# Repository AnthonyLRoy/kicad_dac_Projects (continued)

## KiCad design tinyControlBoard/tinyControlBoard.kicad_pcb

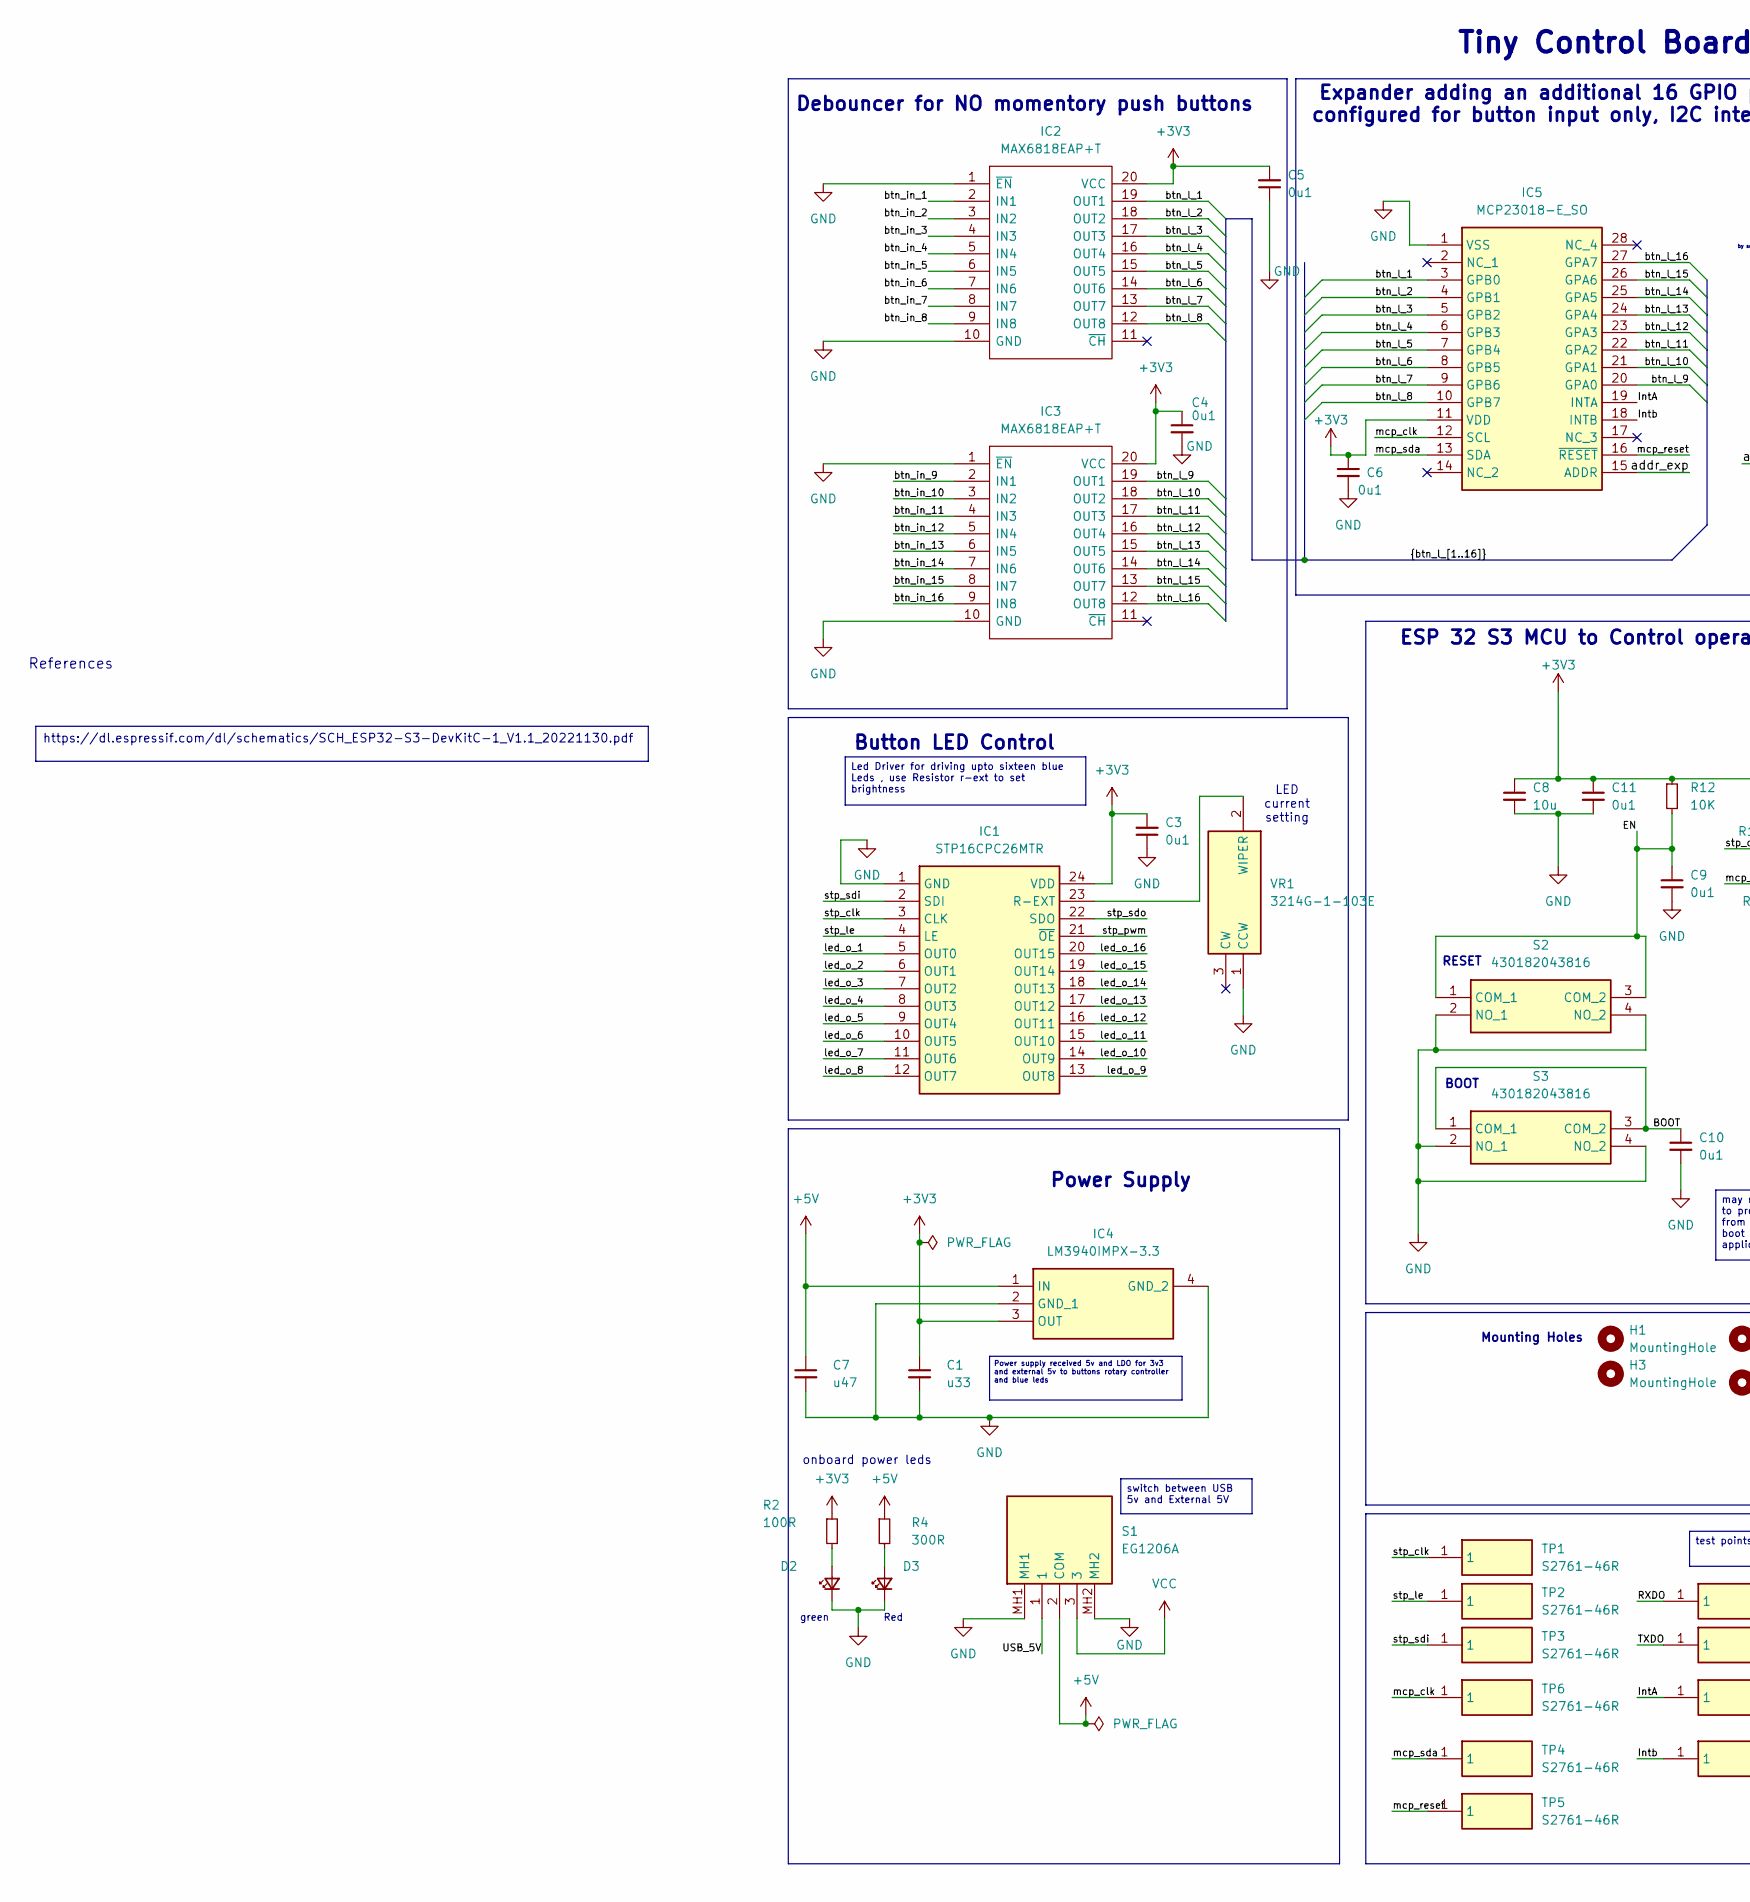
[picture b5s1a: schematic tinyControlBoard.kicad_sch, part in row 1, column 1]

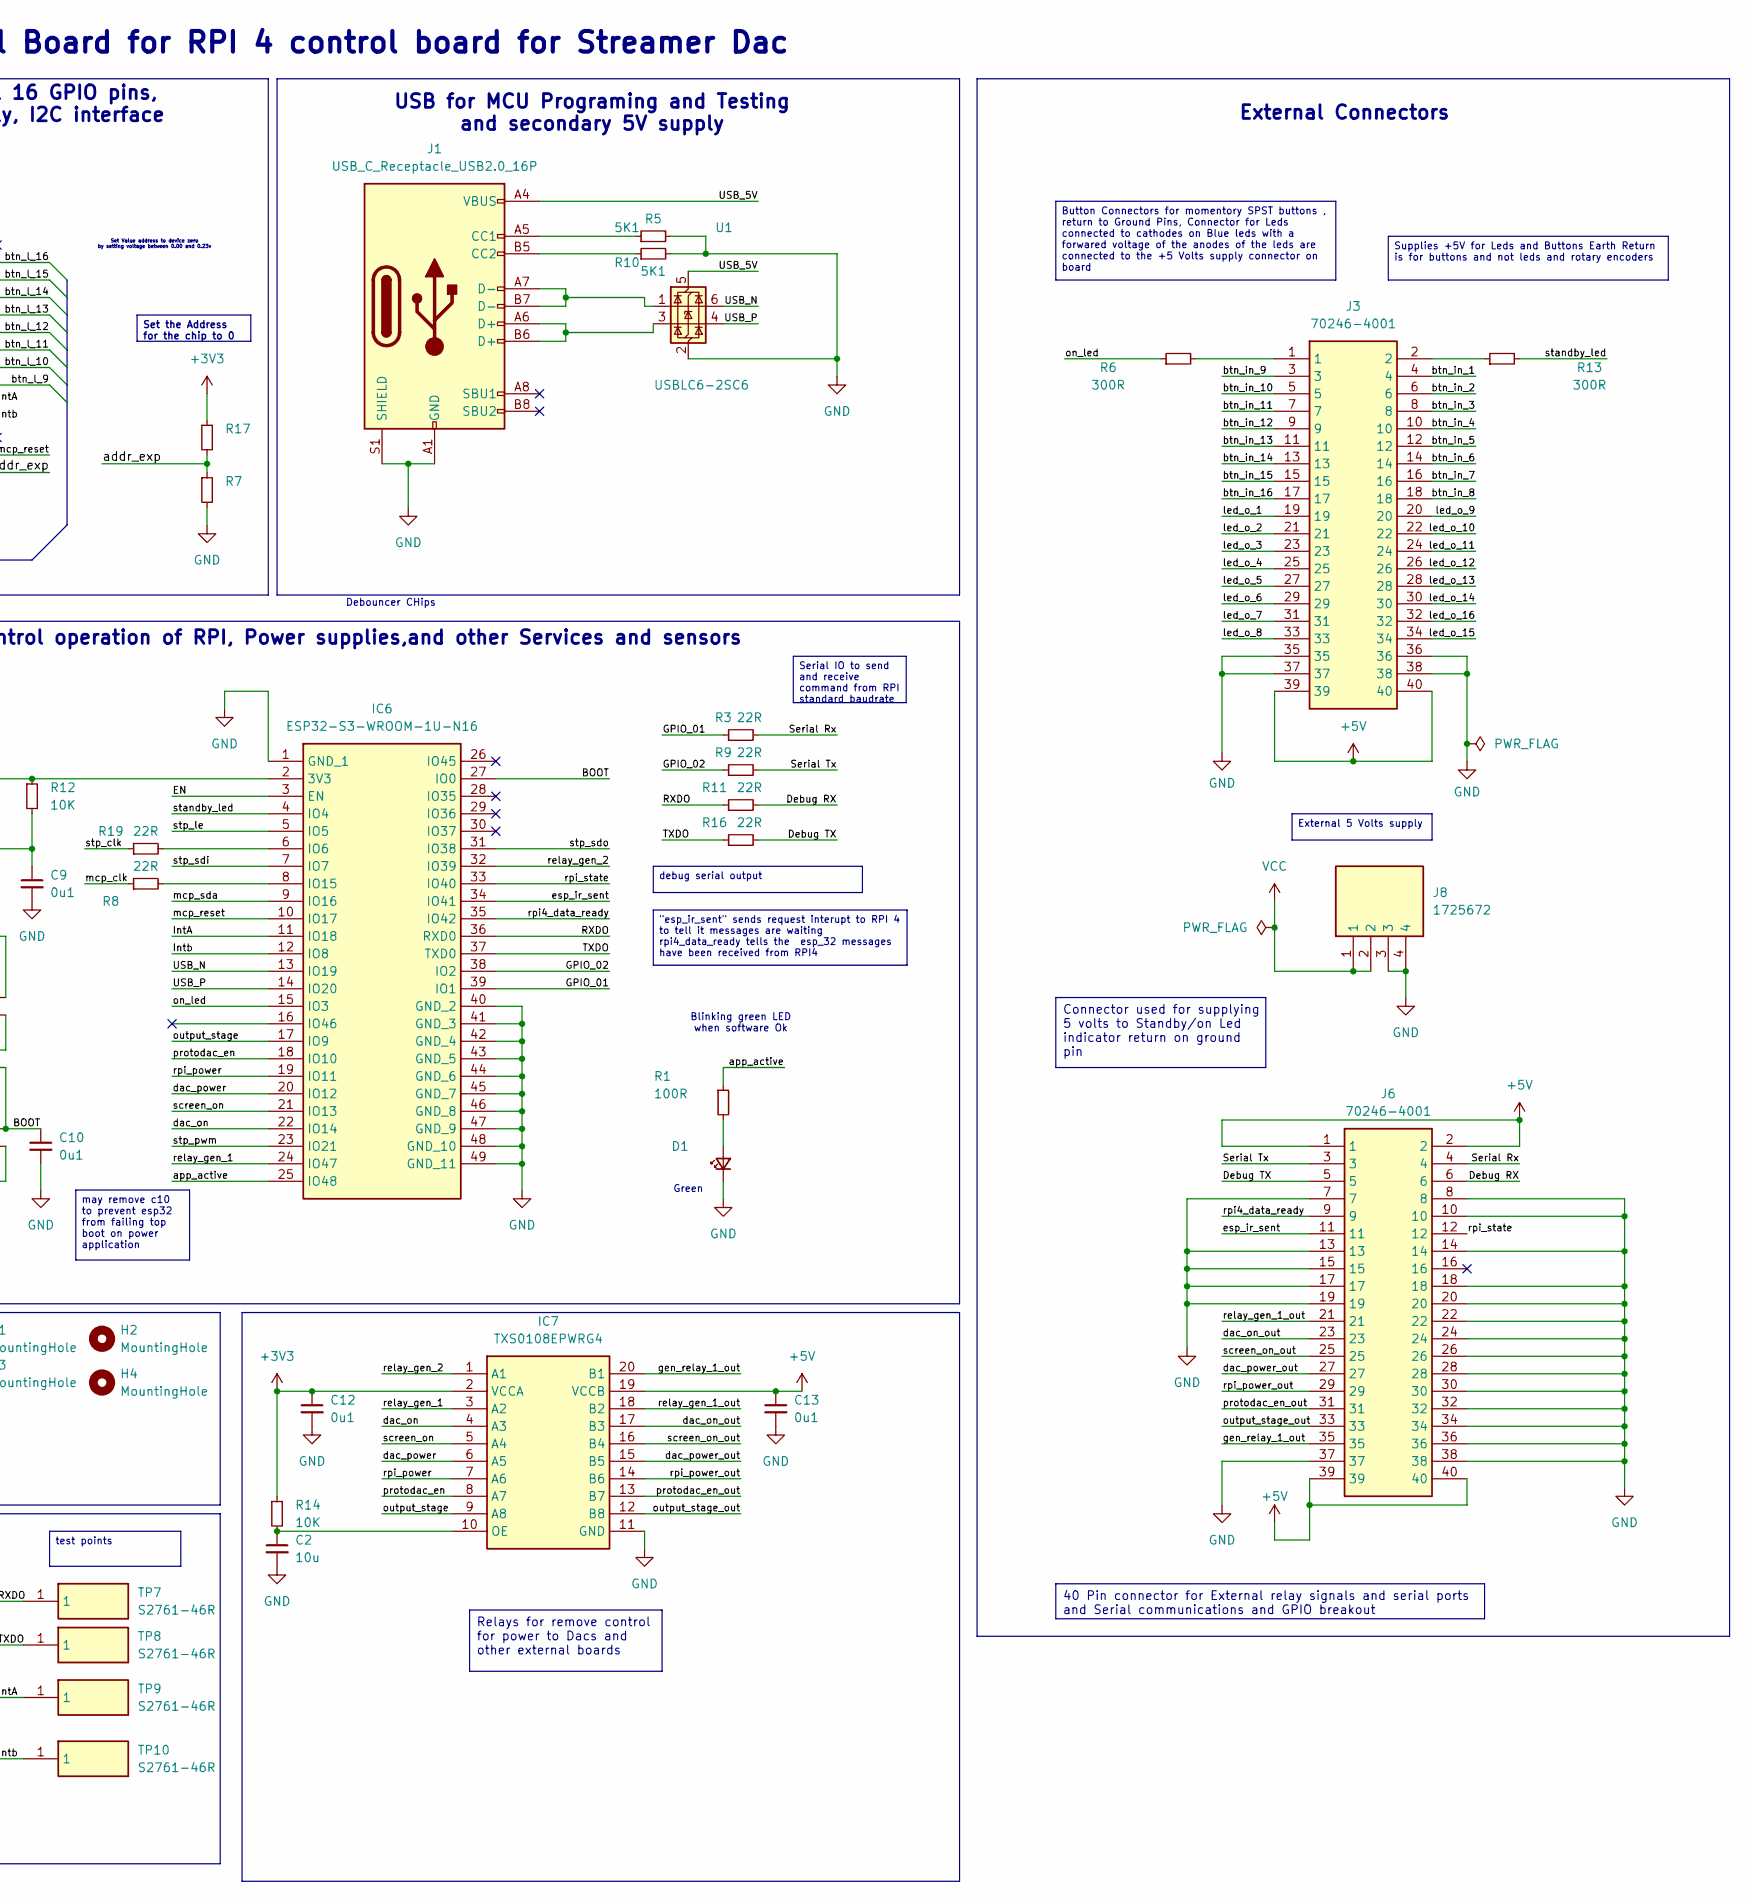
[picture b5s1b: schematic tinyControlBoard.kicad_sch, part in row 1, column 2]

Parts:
C1: u33; CAPC1608X90N; Mouser Part Number 581-0603YC334JAT2A
C2, C8: 10u; CAPC1608X90N; Mouser Part Number 581-0603YD106MAT2A
C3, C4, C5, C6, C9, C10: 0u1; CAPC1608X87N; Manufacturer_Part_Number C0603C104K4RAC3190
C7: u47; CAPC1608X90N; Mouser Part Number 81-GCM188R71C474KA5J
C11, C12, C13: 0u1; CAPC1608X87N; Mouser Part Number 80-C0603C104K4R3190
D1, D2: LG_R971-KN-1; LEDC2012X80N; Mouser Part Number 720-LGR971-KN-1
D3: LS_R976; LEDC2012X40N; Mouser Part Number 720-LSR976D5178
H1, H2, H3, H4: MountingHole; MountingHole_2.5mm
IC1: STP16CPC26MTR; SOIC127P1032X265-24N; Mouser Part Number 511-STP16CPC26MTR
IC2, IC3: MAX6818EAP+T; SSOP-20_5.3x7.2mm_P0.65mm; Manufacturer_Part_Number MAX6818EAP+T; Mouser Part Number 700-MAX6818EAPT
IC4: LM3940IMPX-3.3; SOT230P700X180-4N; Mouser Part Number 926-LM3940IMPX-33
IC5: MCP23018-E_SO; SOIC127P1030X265-28N; Mouser Part Number 579-MCP23018-E/SO
IC6: ESP32-S3-WROOM-1U-N16; ESP32S3WROOM1UN16; Mouser Part Number 356-ESP32S3WROM1UN16
IC7: TXS0108EPWRG4; SOP65P640X120-20N; Mouser Part Number 595-TXS0108EPWRG4
J1: USB_C_Receptacle_USB2.0_16P; USB_C_Receptacle_GCT_USB4105-xx-A_16P_TopMnt_Horizontal; Manufacturer_Part_Number USB4105-GF-A-120; Mouser Part Number 640-USB4105-GF-A-120
J3, J6: 70246-4001; SHDR40W64P254_2X20_5842X889X947P; Mouser Part Number 538-70246-4001
J8: 1725672; Mouser Part Number 651-1725672
R1, R2: 100R; ERJH3; Mouser Part Number 667-ERJ-H3EF1200V
R3, R8, R9, R11, R16, R19: 22R; RESC1609X55N; Mouser Part Number 667-ERJ-P03F22R0V
R4, R6, R13: 300R; ERJH3; Mouser Part Number 667-ERJ-H3ED3000V
R5, R10: 5K1; RESC1608X55N; Mouser Part Number 755-ESR03EZPJ512
R7: MCT0603PD1001DP500; RESC1608X55N; Mouser Part Number 594-MCT0603PD1001DP5
R12, R14: 10K; RESC1608X50N; Mouser Part Number 71-CRCW060310K0FKEI
R17: TNPW060315K0BEEA; RESC1608X60N; Mouser Part Number 71-TNPW060315K0BEEA
S1: EG1206A; Mouser Part Number 612-EG1206A
S2, S3: 430182043816; Mouser Part Number 710-430182043816
TP1, TP2, TP3, TP4, TP5, TP6, TP7, TP8, TP9, TP10: S2761-46R; S276146R; Mouser Part Number 855-S2761-46R
U1: USBLC6-2SC6; SOT-23-6; Manufacturer_Part_Number 511-USBLC6-2SC6; Mouser Part Number USBLC6-2SC6
VR1: 3214G-1-103E; 3214G1103E; Mouser Part Number 652-3214G-1-103E

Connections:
+3V3: C1.1, C3.2, C4.1, C5.2, C6.1, C8.1, C11.1, C12.1, IC1.24 (VDD), IC2.20 (VCC), IC3.20 (VCC), IC4.3 (OUT), IC5.11 (VDD), IC6.2 (3V3), IC7.2 (VCCA), R2.1, R12.1, R14.1, R17.1
+5V: C7.1, C13.1, IC4.1 (IN), IC7.19 (VCCB), J3.39, J3.40, J6.1, J6.2, J6.39, J6.40, R4.1, S1.2 (COM)
/BOOT: C10.1, IC6.27 (IO0), S3.1 (COM_1), S3.3 (COM_2)
/Debug RX: J6.6, R11.2
/Debug TX: J6.5, R16.2
/EN: C9.1, IC6.3 (EN), R12.2, S2.1 (COM_1), S2.3 (COM_2)
/GPIO_01: IC6.39 (IO1), R3.1
/GPIO_02: IC6.38 (IO2), R9.1
/GPIO_39: IC6.32 (IO39), IC7.1 (A1)
/IntA: IC5.19 (INTA), IC6.11 (IO18), TP9.1
/Intb: IC5.18 (INTB), IC6.12 (IO8), TP10.1
/RXDO: IC6.36 (RXD0), R11.1, TP7.1
/Serial Rx: J6.4, R3.2
/Serial Tx: J6.3, R9.2
/TXDO: IC6.37 (TXD0), R16.1, TP8.1
/USB_5V: J1.A4 (VBUS), J1.A9 (VBUS), J1.B4 (VBUS), J1.B9 (VBUS), S1.1, U1.5 (VBUS)
/USB_N: IC6.13 (IO19), U1.6 (I/O1)
/USB_P: IC6.14 (IO20), U1.4 (I/O2)
/addr_exp: IC5.15 (ADDR), R7.1, R17.2
/app_active: IC6.25 (IO48), R1.1
/btn_in_1: IC2.2 (IN1), J3.4
/btn_in_2: IC2.3 (IN2), J3.6
/btn_in_3: IC2.4 (IN3), J3.8
/btn_in_4: IC2.5 (IN4), J3.10
/btn_in_5: IC2.6 (IN5), J3.12
/btn_in_6: IC2.7 (IN6), J3.14
/btn_in_7: IC2.8 (IN7), J3.16
/btn_in_8: IC2.9 (IN8), J3.18
/btn_in_9: IC3.2 (IN1), J3.3
/btn_in_10: IC3.3 (IN2), J3.5
/btn_in_11: IC3.4 (IN3), J3.7
/btn_in_12: IC3.5 (IN4), J3.9
/btn_in_13: IC3.6 (IN5), J3.11
/btn_in_14: IC3.7 (IN6), J3.13
/btn_in_15: IC3.8 (IN7), J3.15
/btn_in_16: IC3.9 (IN8), J3.17
/btn_l_1: IC2.19 (OUT1), IC5.3 (GPB0)
/btn_l_2: IC2.18 (OUT2), IC5.4 (GPB1)
/btn_l_3: IC2.17 (OUT3), IC5.5 (GPB2)
/btn_l_4: IC2.16 (OUT4), IC5.6 (GPB3)
/btn_l_5: IC2.15 (OUT5), IC5.7 (GPB4)
/btn_l_6: IC2.14 (OUT6), IC5.8 (GPB5)
/btn_l_7: IC2.13 (OUT7), IC5.9 (GPB6)
/btn_l_8: IC2.12 (OUT8), IC5.10 (GPB7)
/btn_l_9: IC3.19 (OUT1), IC5.20 (GPA0)
/btn_l_10: IC3.18 (OUT2), IC5.21 (GPA1)
/btn_l_11: IC3.17 (OUT3), IC5.22 (GPA2)
/btn_l_12: IC3.16 (OUT4), IC5.23 (GPA3)
/btn_l_13: IC3.15 (OUT5), IC5.24 (GPA4)
/btn_l_14: IC3.14 (OUT6), IC5.25 (GPA5)
/btn_l_15: IC3.13 (OUT7), IC5.26 (GPA6)
/btn_l_16: IC3.12 (OUT8), IC5.27 (GPA7)
/dac_on: IC6.22 (IO14), IC7.4 (A3)
/dac_on_out: IC7.17 (B3), J6.23
/esp_ir_sent: IC6.34 (IO41), J6.11
/gen_relay_1_out: IC7.20 (B1), J6.35
/gen_relay_2: IC6.18 (IO10), IC7.8 (A7)
/gen_relay_2_out: IC7.13 (B7), J6.31
/gen_relay_3: IC6.17 (IO9), IC7.9 (A8)
/gen_relay_3_out: IC7.12 (B8), J6.33
/gen_relay_4: IC6.24 (IO47), IC7.3 (A2)
/gen_relay_4_out: IC7.18 (B2), J6.21
/led_o_1: IC1.5 (OUT0), J3.19
/led_o_2: IC1.6 (OUT1), J3.21
/led_o_3: IC1.7 (OUT2), J3.23
/led_o_4: IC1.8 (OUT3), J3.25
/led_o_5: IC1.9 (OUT4), J3.27
/led_o_6: IC1.10 (OUT5), J3.29
/led_o_7: IC1.11 (OUT6), J3.31
/led_o_8: IC1.12 (OUT7), J3.33
/led_o_9: IC1.13 (OUT8), J3.20
/led_o_10: IC1.14 (OUT9), J3.22
/led_o_11: IC1.15 (OUT10), J3.24
/led_o_12: IC1.16 (OUT11), J3.26
/led_o_13: IC1.17 (OUT12), J3.28
/led_o_14: IC1.18 (OUT13), J3.30
/led_o_15: IC1.19 (OUT14), J3.34
/led_o_16: IC1.20 (OUT15), J3.32
/mains_power: IC6.19 (IO11), IC7.7 (A6)
/mains_power_out: IC7.14 (B6), J6.29
/mcp_clk: IC5.12 (SCL), R8.1, TP6.1
/mcp_reset: IC5.16 (~RESET), IC6.10 (IO17), TP5.1
/mcp_sda: IC5.13 (SDA), IC6.9 (IO16), TP4.1
/on_led: IC6.15 (IO3), R6.1
/rpi4_data_ready: IC6.35 (IO42), J6.9
/rpi_state: IC6.33 (IO40), J6.12
/screen_on: IC6.21 (IO13), IC7.5 (A4)
/screen_on_out: IC7.16 (B4), J6.25
/standby_led: IC6.4 (IO4), R13.2
/stp_clk: IC1.3 (CLK), R19.1, TP1.1
/stp_le: IC1.4 (LE), IC6.5 (IO5), TP2.1
/stp_pwm: IC1.21 (~OE), IC6.23 (IO21)
/stp_sdi: IC1.2 (SDI), IC6.7 (IO7), TP3.1
/stp_sdo: IC1.22 (SDO), IC6.31 (IO38)
/switch_dac: IC6.20 (IO12), IC7.6 (A5)
/switch_dac_out: IC7.15 (B5), J6.27
GND: C1.2, C2.2, C3.1, C4.2, C5.1, C6.2, C7.2, C8.2, C9.2, C10.2, C11.2, C12.2, C13.2, D1.1 (K), D2.1 (K), D3.1 (K), IC1.1 (GND), IC2.1 (~EN), IC2.10 (GND), IC3.1 (~EN), IC3.10 (GND), IC4.2 (GND_1), IC4.4 (GND_2), IC5.1 (VSS), IC6.1 (GND_1), IC6.40 (GND_2), IC6.41 (GND_3), IC6.42 (GND_4), IC6.43 (GND_5), IC6.44 (GND_6), IC6.45 (GND_7), IC6.46 (GND_8), IC6.47 (GND_9), IC6.48 (GND_10), IC6.49 (GND_11), IC7.11 (GND), J1.A1 (GND), J1.A12 (GND), J1.B1 (GND), J1.B12 (GND), J1.S1 (SHIELD), J3.35, J3.36, J3.37, J3.38, J6.7, J6.8, J6.10, J6.13, J6.14, J6.15, J6.17, J6.18, J6.19, J6.20, J6.22, J6.24, J6.26, J6.28, J6.30, J6.32, J6.34, J6.36, J6.37, J6.38, J8.3, J8.4, R5.2, R7.2, R10.2, S1.MH1, S1.MH2, S2.2 (NO_1), S2.4 (NO_2), S3.2 (NO_1), S3.4 (NO_2), U1.2 (GND), VR1.1 (CCW)
unnamed: D1.2 (A), R1.2
unnamed: D2.2 (A), R2.2
unnamed: D3.2 (A), R4.2
unnamed: IC1.23 (R-EXT), VR1.2 (WIPER)
unnamed: IC6.6 (IO6), R19.2
unnamed: IC6.8 (IO15), R8.2
unnamed: C2.1, IC7.10 (OE), R14.2
unnamed: J1.A5 (CC1), R5.1
unnamed: J1.B5 (CC2), R10.1
unnamed: J1.A6 (D+), J1.B6 (D+), U1.3 (I/O2)
unnamed: J1.A7 (D-), J1.B7 (D-), U1.1 (I/O1)
unnamed: J3.1, R6.2
unnamed: J3.2, R13.1
VCC: J8.1, J8.2, S1.3

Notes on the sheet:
Green
References
Set Value address to device zero by setting voltage between 0.00 and 0.23v
onboard power leds
BOOT
USB for MCU Programing and Testing and secondary 5V supply
Debouncer CHips
Mounting Holes
Expander adding an additional 16 GPIO pins, configured for button input only, I2C interface
Debouncer for NO momentory push buttons
RESET
Tiny Control Board for RPI 4 control board for Streamer Dac
Power Supply
Button LED Control
Red
ESP 32 S3 MCU to Control operation of RPI, Power supplies,and other Services and sensors
Blinking green LED when software Ok
green
LED current setting
External Connectors
Connector used for supplying 5 volts to Standby/on Led indicator return on ground pin
https://dl.espressif.com/dl/schematics/SCH_ESP32-S3-DevKitC-1_V1.1_20221130.pdf
External 5 Volts supply
Supplies +5V for Leds and Buttons Earth Return is for buttons and not leds and rotary encoders
Serial IO to send and receive command from RPI standard baudrate
40 Pin connector for External relay signals and serial ports and Serial communications and GPIO breakout
debug serial output
switch between USB 5v and External 5V
Power supply received 5v and LDO for 3v3 and external 5v to buttons rotary controller and blue leds
Set the Address for the chip to 0
"esp_ir_sent" sends request interupt to RPI 4 to tell it messages are waiting rpi4_data_ready tells the esp_32 messages have been received from RPI4
Relays for remove control for power to Dacs and other external boards
test points
Button Connectors for momentory SPST buttons , return to Ground Pins, Connector for Leds connected to cathodes on Blue leds with a forwared voltage of the anodes of the leds are connected to the +5 Volts supply connector on board
Led Driver for driving upto sixteen blue Leds , use Resistor r-ext to set brightness
may remove c10 to prevent esp32 from failing top boot on power application

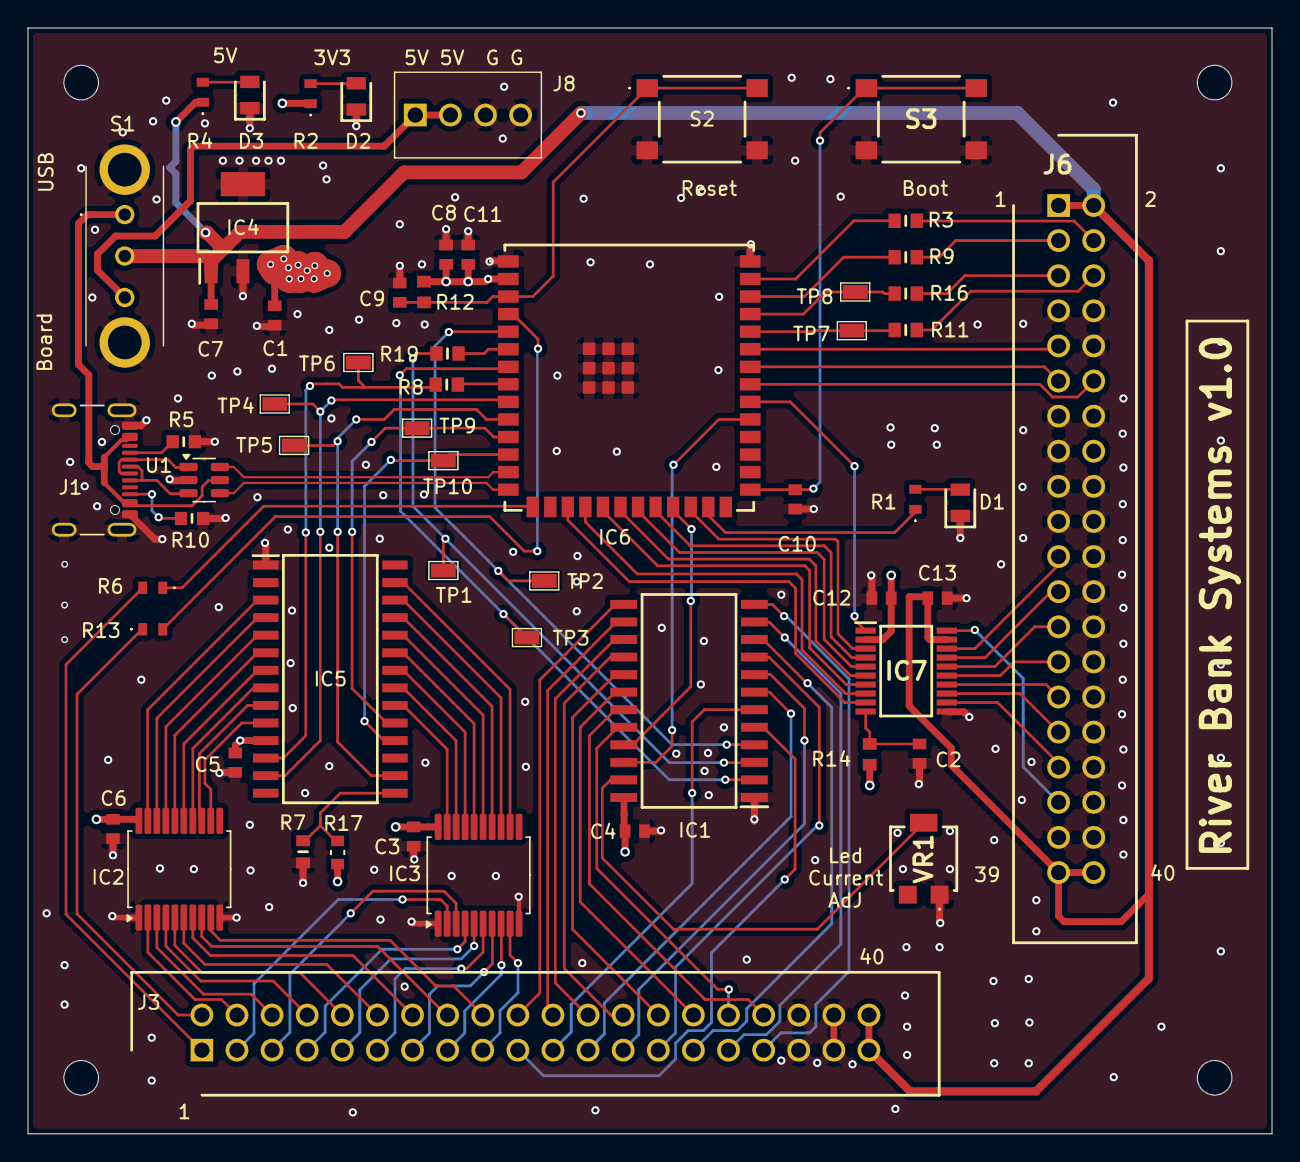
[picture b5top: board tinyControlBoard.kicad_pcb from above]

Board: 4 copper layers, 90.0 x 80.0 mm, 63 parts (0 on the bottom side), 111 nets.

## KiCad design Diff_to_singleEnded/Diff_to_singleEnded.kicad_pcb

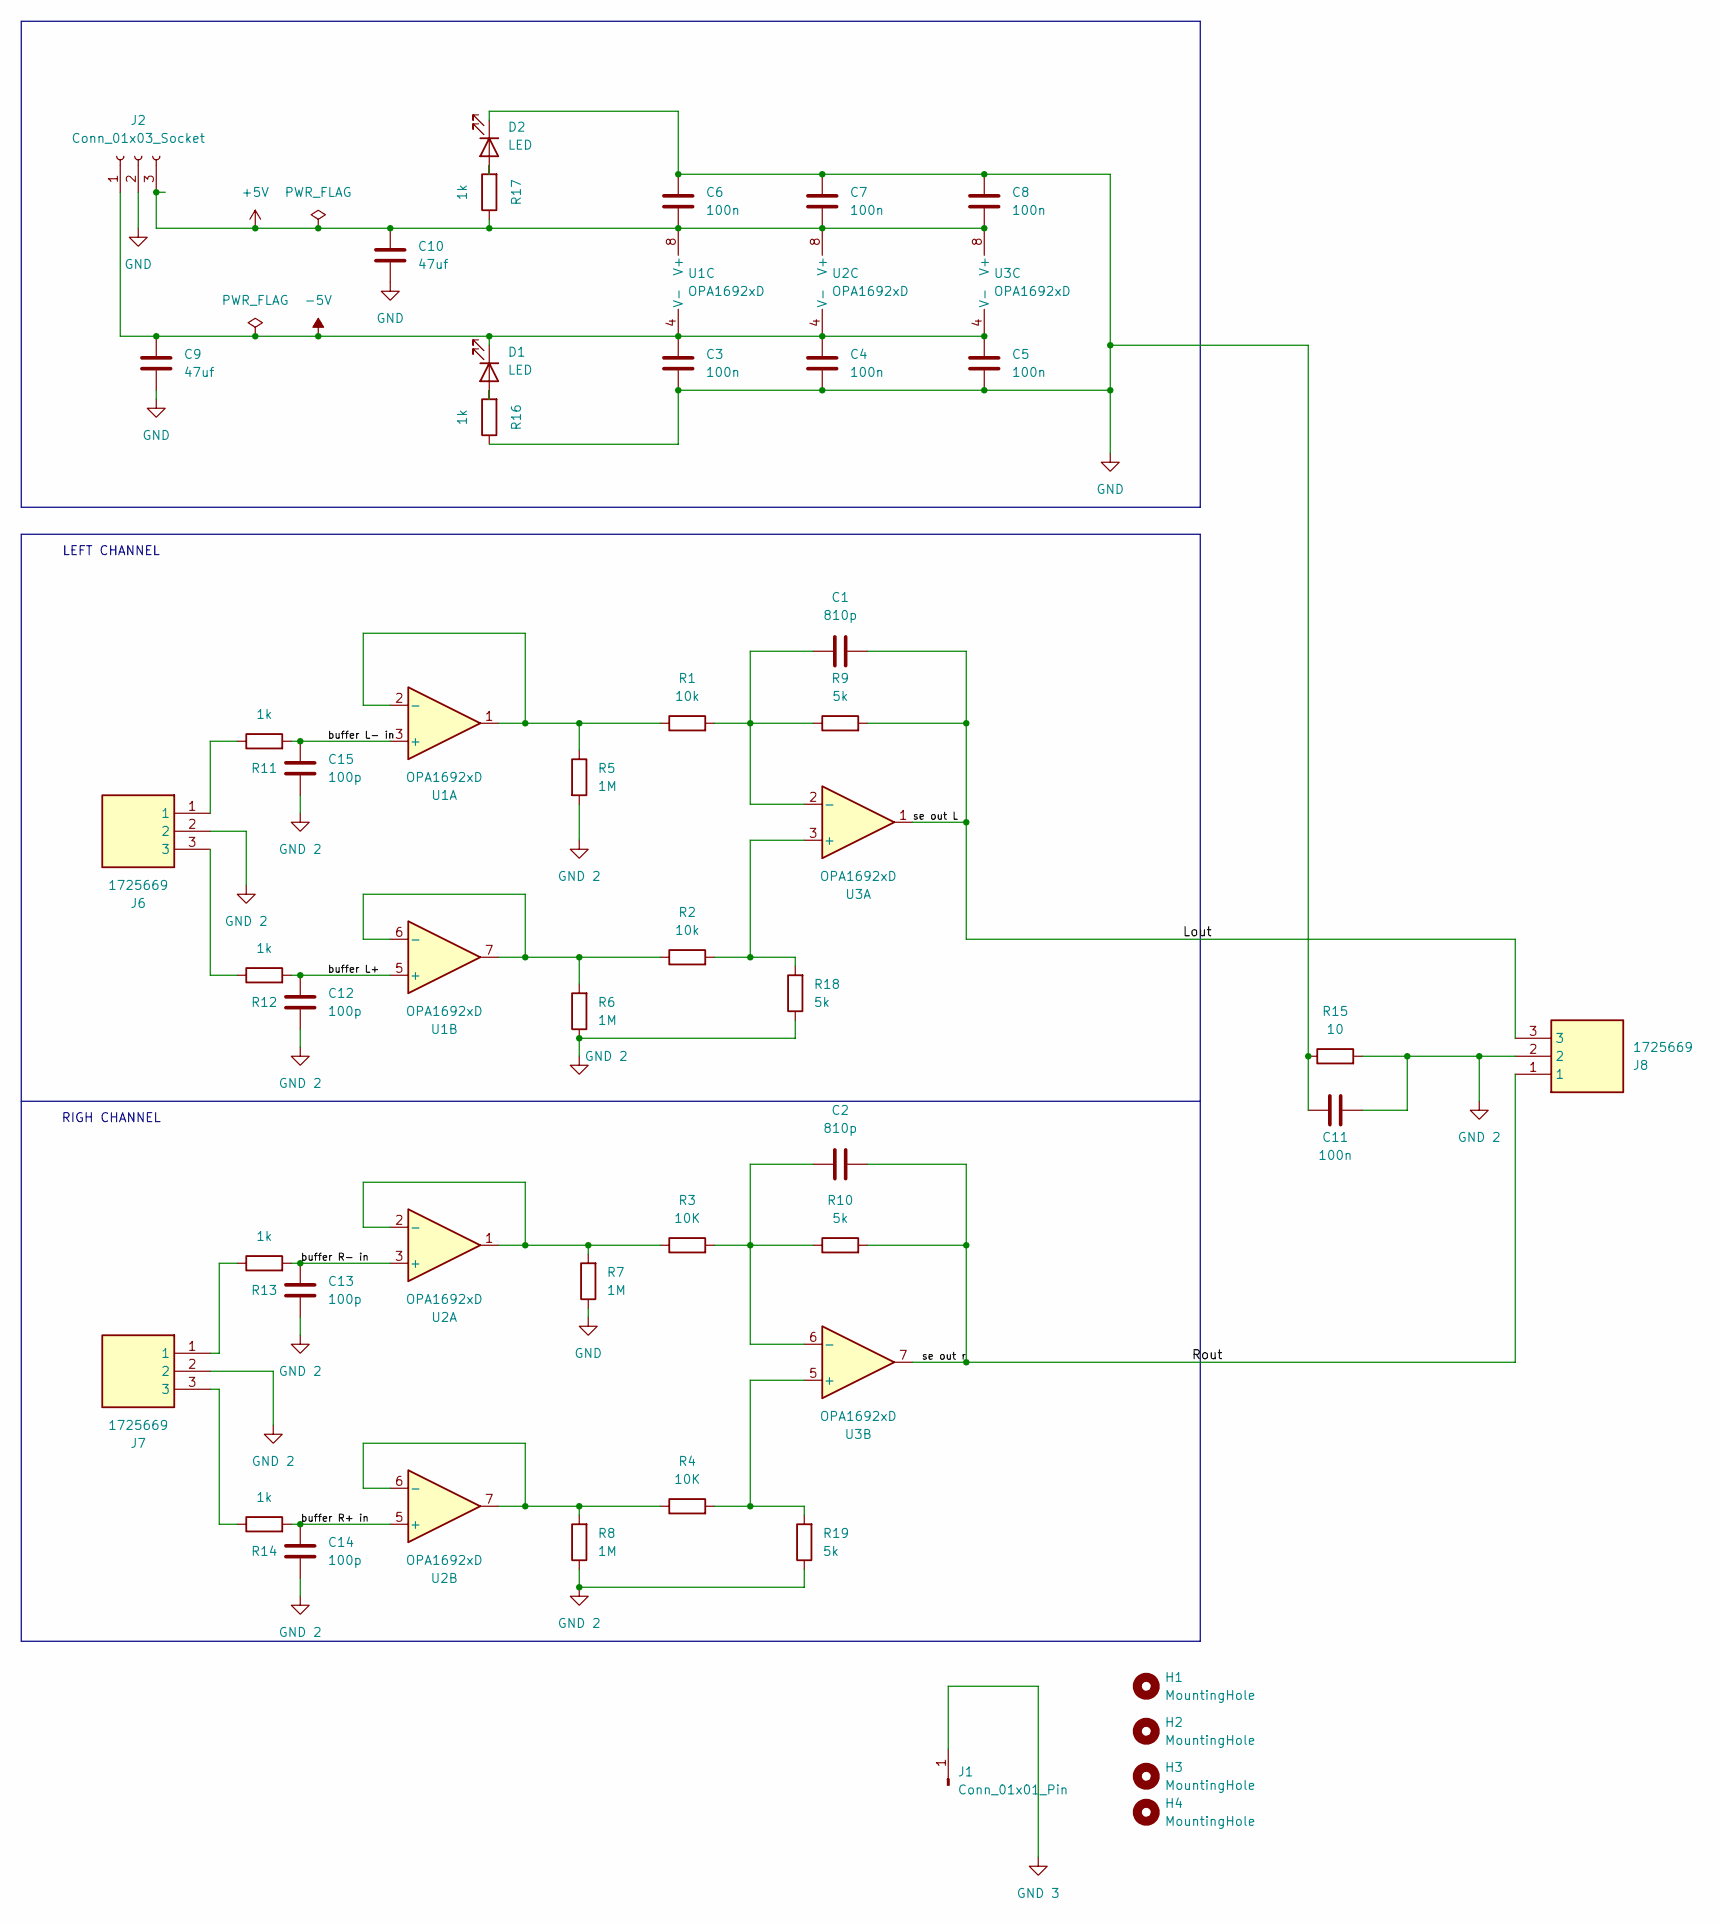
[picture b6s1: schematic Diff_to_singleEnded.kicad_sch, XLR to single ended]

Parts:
C1, C2: 810p; C_1206_3216Metric
C3, C4, C5, C6, C7, C8, C11: 100n; C_0805_2012Metric_Pad1.18x1.45mm_HandSolder
C9, C10: 47uf; CAPC3225X280N
C12, C13, C14, C15: 100p; C_0805_2012Metric
D1, D2: LED; LEDC2012X40N
H1, H2, H3, H4: MountingHole; MountingHole_2.7mm_M2.5
J1: Conn_01x01_Pin; PinHeader_1x01_P1.00mm_Vertical
J2: Conn_01x03_Socket; PhoenixContact_MCV_1,5_3-G-3.81_1x03_P3.81mm_Vertical
J6, J7, J8: 1725669; Mouser Part Number 651-1725669
R1, R2: 10k; R_Axial_DIN0309_L9.0mm_D3.2mm_P12.70mm_Horizontal
R3, R4: 10K; R_Axial_DIN0309_L9.0mm_D3.2mm_P12.70mm_Horizontal
R5, R6, R7, R8: 1M; R_Axial_DIN0309_L9.0mm_D3.2mm_P12.70mm_Horizontal
R9, R10, R18, R19: 5k; R_Axial_DIN0309_L9.0mm_D3.2mm_P12.70mm_Horizontal
R11, R12, R13, R14, R16, R17: 1k; R_0805_2012Metric
R15: 10; R_0603_1608Metric
U1, U2, U3: OPA1692xD; SOIC-8_3.9x4.9mm_P1.27mm

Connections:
+5V: C6.2, C7.2, C8.2, C10.1, J2.3, R17.1, U1.8 (V+), U2.8 (V+), U3.8 (V+)
-5V: C3.1, C4.1, C5.1, C9.1, D1.1 (K), J2.1, U1.4 (V-), U2.4 (V-), U3.4 (V-)
/Lout: C1.2, J8.3, R9.2, U3.1
/Rout: C2.2, J8.1, R10.2, U3.7
/buffer L+: C12.2, R12.2, U1.5 (+)
/buffer L- in: C15.2, R11.2, U1.3 (+)
/buffer R+ in: C14.2, R14.2, U2.5 (+)
/buffer R- in: C13.2, R13.2, U2.3 (+)
GND: C3.2, C4.2, C5.2, C6.1, C7.1, C8.1, C9.2, C10.2, C11.1, D2.1 (K), J2.2, R7.1, R15.1, R16.1
GND 2: C11.2, C12.1, C13.1, C14.1, C15.1, J6.2, J7.2, J8.2, R5.2, R6.1, R8.1, R15.2, R18.1, R19.1
GND 3: J1.1 (Pin_1_1)
unnamed: D1.2 (A), R16.2
unnamed: D2.2 (A), R17.2
unnamed: J6.1, R11.1
unnamed: J6.3, R12.1
unnamed: J7.1, R13.1
unnamed: J7.3, R14.1
unnamed: R1.1, R5.1, U1.1, U1.2 (-)
unnamed: R2.1, R6.2, U1.6 (-), U1.7
unnamed: R3.1, R7.2, U2.1, U2.2 (-)
unnamed: R4.1, R8.2, U2.6 (-), U2.7
unnamed: R2.2, R18.2, U3.3 (+)
unnamed: C1.1, R1.2, R9.1, U3.2 (-)
unnamed: R4.2, R19.2, U3.5 (+)
unnamed: C2.1, R3.2, R10.1, U3.6 (-)

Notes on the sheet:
LEFT CHANNEL
RIGH CHANNEL

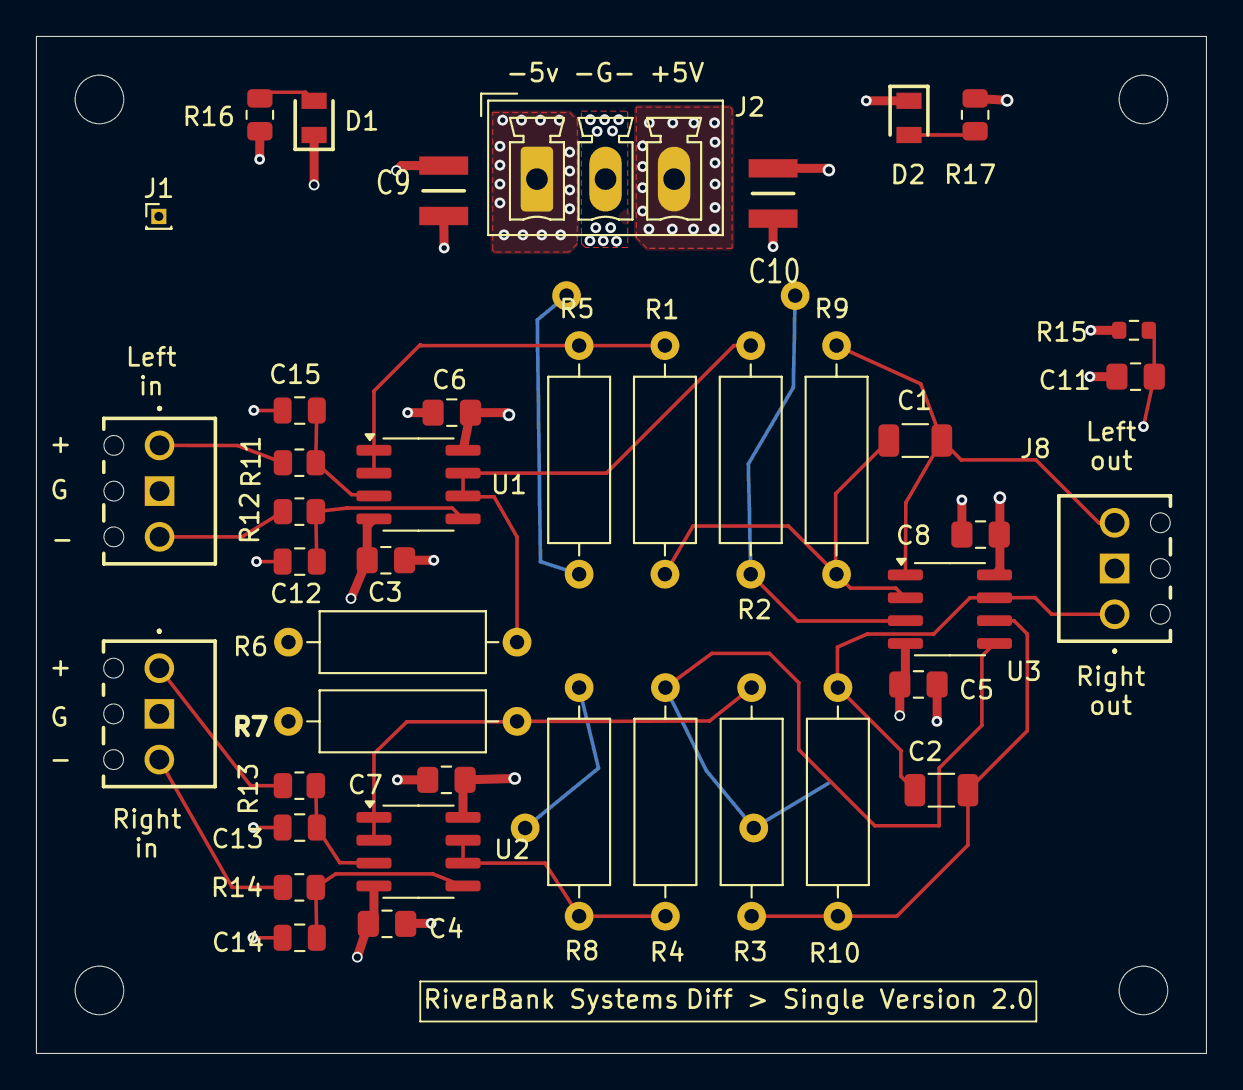
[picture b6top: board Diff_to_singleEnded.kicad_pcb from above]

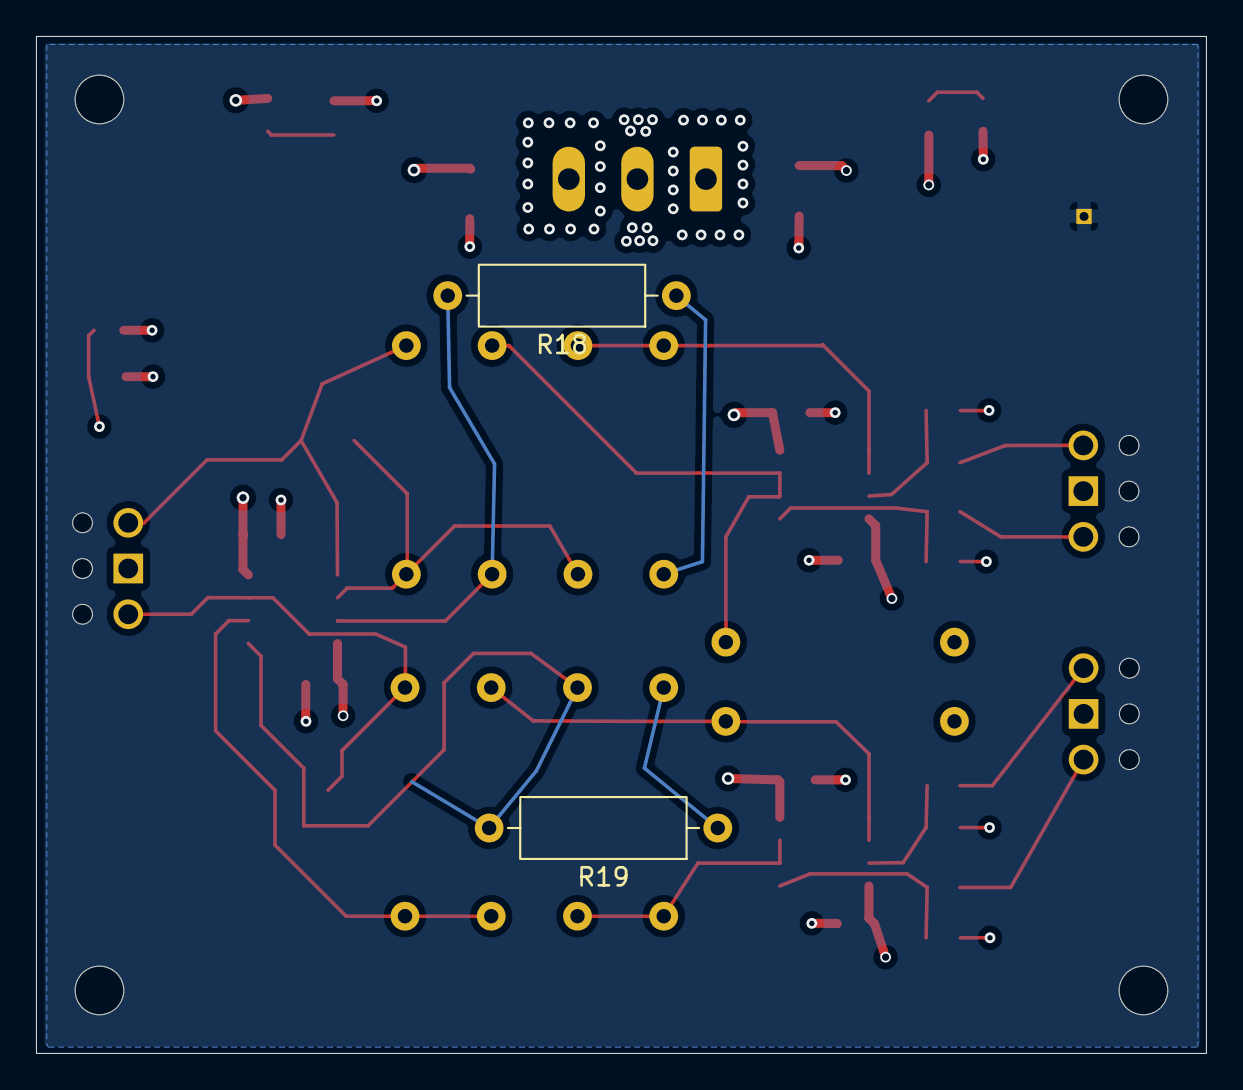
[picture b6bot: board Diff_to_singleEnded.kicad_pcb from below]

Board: 6 copper layers, 65.0 x 56.5 mm, 48 parts (2 on the bottom side), 24 nets.

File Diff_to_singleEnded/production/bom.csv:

Designator,Footprint,Quantity,Value,LCSC Part #
"C1, C2",1206,2,810p,
"C10, C9",CAPC3225X280N,2,47uf,
"C11, C3, C4, C5, C6, C7, C8",0805,7,100n,
"C12, C13, C14, C15",0805,4,100p,
"D1, D2",LEDC2012X40N,2,LED,
"H1, H2, H3, H4",MountingHole_2.7mm_M2.5,4,MountingHole,
J1,PinHeader_1x01_P1.00mm_Vertical,1,Conn_01x01_Pin,
J2,"PhoenixContact_MCV_1,5_3-G-3.81_1x03_P3.81mm_Vertical",1,Conn_01x03_Socket,
"J6, J7, J8",1725669,3,1725669,
"R1, R2, R3, R4",R_Axial_DIN0309_L9.0mm_D3.2mm_P12.70mm_Horizontal,4,10k,
"R10, R9",R_Axial_DIN0309_L9.0mm_D3.2mm_P12.70mm_Horizontal,2,5k,
"R11, R12, R13, R14, R16, R17",0805,6,1k,
R15,0603,1,10,
"R5, R6, R7, R8",R_Axial_DIN0309_L9.0mm_D3.2mm_P12.70mm_Horizontal,4,1M,
"U1, U2, U3",SOIC-8_3.9x4.9mm_P1.27mm,3,OPA1692xD,
